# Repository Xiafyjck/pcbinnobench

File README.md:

# PCBInnoBench

PCBInnoBench is an executable PCB design benchmark for LLM agents. This release contains a curated 35-task subset packaged for Forge runs. Each task asks an agent to modify a KiCad project in place and is evaluated against hidden task validators.

## Repository Layout

- `tasks/`: 35 agent-visible task packages. Each task contains `workspace/`, `prompt.md`, `prompt_with_guidance.md`, and `task.json`; original component PDFs remain under each task workspace when available.
- `evaluation/ground_truths/`: hidden golden KiCad projects used only by validators. Do not copy this directory into an agent sandbox.
- `validators/common/`: shared validator implementation.
- `validators/tasks/`: thin per-task validators that call the shared validator with task-specific file expectations.
- `scripts/create_sandboxes.py`: creates isolated Forge sandboxes.
- `scripts/run_forge.py`: runs Forge on prepared sandboxes.
- `scripts/validate.py`: scores completed sandboxes.

## Run With Forge

Create base-prompt sandboxes:

```bash
uv run python scripts/create_sandboxes.py --variant base --tasks all --out runs/forge_base_35
```

Create guided-prompt sandboxes:

```bash
uv run python scripts/create_sandboxes.py --variant guidance --tasks all --out runs/forge_guidance_35
```

Run Forge:

```bash
uv run python scripts/run_forge.py --root runs/forge_guidance_35 --workers 8 --timeout 5400
```

Score the run:

```bash
uv run python scripts/validate.py --run runs/forge_guidance_35 --write
```

Forge model/provider selection is intentionally left to your Forge configuration. The runner records the selected model label if you pass `--model`, but it does not call Codex CLI or Claude Code.

## Task Format

A task directory has this shape:

```text
tasks/<task_id>/
├── workspace/
├── prompt.md
├── prompt_with_guidance.md
└── task.json
```

`workspace/` is the only directory the evaluated agent should edit. The `prompt_with_guidance.md` file is the guided condition described in the benchmark paper.

## Validator Boundary

The public validator code is split into a maintained common layer and small task-specific wrappers. The hidden golden projects live under `evaluation/ground_truths/` and are intentionally excluded from sandboxes produced by `create_sandboxes.py`.

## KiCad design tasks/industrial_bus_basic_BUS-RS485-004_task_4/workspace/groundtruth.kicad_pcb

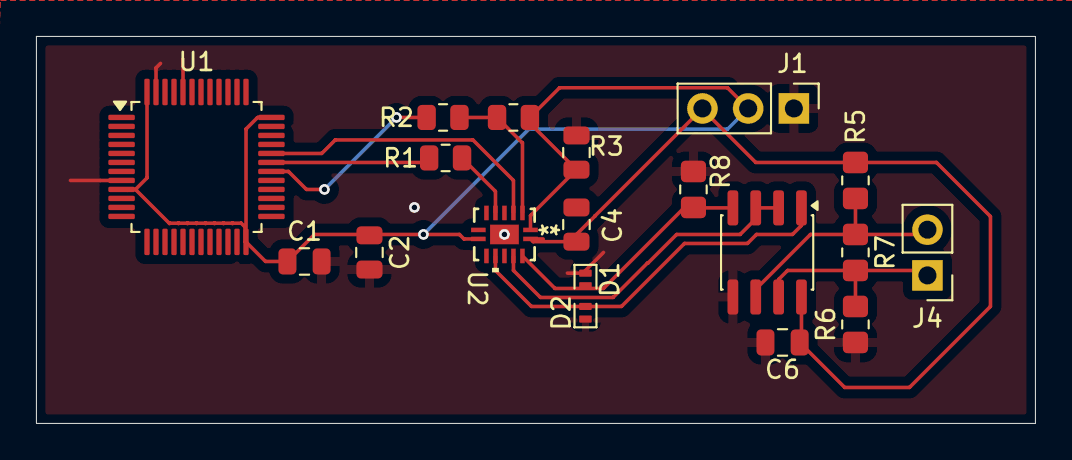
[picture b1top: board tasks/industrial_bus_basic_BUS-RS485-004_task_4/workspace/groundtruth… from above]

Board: 2 copper layers, 55.5 x 21.5 mm, 19 parts (0 on the bottom side), 13 nets.

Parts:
C1, C4, C5: 0.1uf; C_0805_2012Metric
C2: 1uf; C_0805_2012Metric
C6: 2.2uf; C_0805_2012Metric
D1, D2: PESD5V0L1UL; D_SOD-882
J1: Conn_01x03_Pin; PinHeader_1x03_P2.54mm_Vertical
J4: Conn_01x02_Pin; PinHeader_1x02_P2.54mm_Vertical
R1, R2: 50; R_0805_2012Metric
R3: 10k; R_0805_2012Metric
R5, R6: 7.4K; R_0805_2012Metric_Pad1.20x1.40mm_HandSolder
R7: 120; R_0805_2012Metric_Pad1.20x1.40mm_HandSolder
R8: 4.7K; R_0805_2012Metric_Pad1.20x1.40mm_HandSolder
U1: STM32F103C8Tx; LQFP-48_7x7mm_P0.5mm
U2: TXU0304BQAR; QFN_04BQAR_TEX
U3: MAX485E; SOIC-8_3.9x4.9mm_P1.27mm

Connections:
+3V3: C1.1, C2.1, C5.1, J1.2, R3.2, U1.9 (VDDA), U1.24 (VDD), U1.36 (VDD), U1.48 (VDD), U2.1 (VCCA), U2.8 (OE)
+5V: C4.1, C6.2, J1.3, R5.2, U2.14 (VCCB), U3.8 (VCC)
/RS485_5V/RS485_2A: J4.2, R5.1, R7.1, U3.6 (A)
/RS485_5V/RS485_2B: J4.1, R6.2, R7.2, U3.7 (B)
/RS485_5V/RS485_2_DE: U2.12 (B2Y), U3.2 (~RE), U3.3 (DE)
/RS485_5V/RS485_2_RX: D2.2 (A), U2.10 (B4), U3.1 (RO)
/RS485_5V/RS485_2_TX: D1.2 (A), R8.2, U2.13 (B1Y), U3.4 (DI)
/stm32-uart/DE: U1.32 (PA11), U2.3 (A2)
/stm32-uart/RX: R1.2, U2.5 (A4Y)
/stm32-uart/TX: R2.2, R3.1, U2.2 (A1)
GND: C1.2, C2.2, C4.2, C5.2, C6.1, D1.1 (K), D2.1 (K), J1.1, R6.1, R8.1, U1.8 (VSSA), U1.23 (VSS), U1.35 (VSS), U1.44 (BOOT0), U1.47 (VSS), U2.7 (GND), U2.15 (EPAD), U3.5 (GND)
unnamed: R2.1, U1.30 (PA9)
unnamed: R1.1, U1.31 (PA10)

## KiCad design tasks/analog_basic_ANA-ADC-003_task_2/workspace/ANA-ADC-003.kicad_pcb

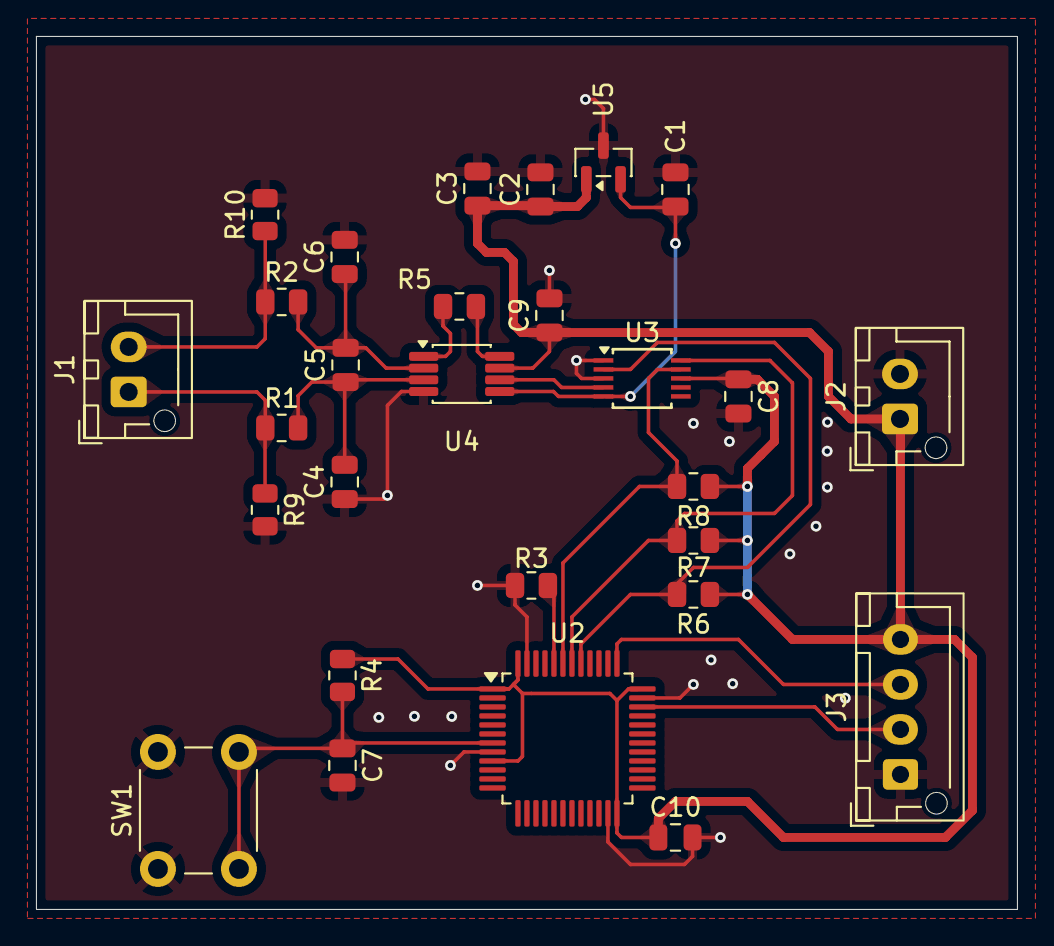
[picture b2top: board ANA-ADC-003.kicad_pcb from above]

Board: 2 copper layers, 54.5 x 48.5 mm, 28 parts (0 on the bottom side), 17 nets.

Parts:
C1: 10uF; C_0805_2012Metric
C2, C8, C9: 0.1uF; C_0805_2012Metric
C3: 1uF; C_0805_2012Metric
C4, C5, C6: 1nF; C_0805_2012Metric
C7, C10: 100nF; C_0805_2012Metric
J1, J2: Conn_01x02_Pin; JST_XH_B2B-XH-AM_1x02_P2.50mm_Vertical
J3: Conn_01x04_Pin; JST_XH_B4B-XH-AM_1x04_P2.50mm_Vertical
R1, R2, R3, R4, R6: 10k; R_0805_2012Metric
R5: 100k; R_0805_2012Metric
R7, R8: 4.7k; R_0805_2012Metric
R9, R10: 10Ω; R_0805_2012Metric
SW1: SW_Push; SW_PUSH_6mm
U2: STM32F103C8Tx; LQFP-48_7x7mm_P0.5mm
U3: ADS1115IDGS; TSSOP-10_3x3mm_P0.5mm
U4: INA333xxDGK; VSSOP-8_3x3mm_P0.65mm
U5: REF3012; SOT-23

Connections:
+3.3V: C2.1, C3.1, C8.1, C9.1, C10.1, J2.1, J3.4, R4.1, R6.1, R7.1, R8.1, U2.1 (VBAT), U2.9 (VDDA), U2.24 (VDD), U2.36 (VDD), U2.48 (VDD), U3.8 (VDD), U4.7 (V+), U5.1 (IN)
/ADC_HIN: J1.1, R1.1, R9.1
/ADC_LIN: J1.2, R2.1, R10.1
/stm32/ADS_ALERT: R6.2, U2.41 (PB5), U3.2 (ALERT/RDY)
/stm32/BOOT0: R3.1, U2.44 (BOOT0)
/stm32/I2C1_SCL: R7.2, U2.42 (PB6), U3.10 (SCL)
/stm32/I2C1_SDA: R8.2, U2.43 (PB7), U3.9 (SDA)
/stm32/NRST: C7.1, R4.2, SW1.2, U2.7 (NRST)
/stm32/swclk: J3.3, U2.37 (PA14)
/stm32/swdio: J3.2, U2.34 (PA13)
/vref: C1.1, U3.5 (AIN1), U4.5 (Ref), U5.2 (OUT)
GND: C1.2, C2.2, C3.2, C4.1, C6.2, C7.2, C8.2, C9.2, C10.2, J2.2, J3.1, R3.2, R9.2, R10.2, SW1.1, U2.8 (VSSA), U2.23 (VSS), U2.35 (VSS), U2.47 (VSS), U3.1 (ADDR), U3.3 (GND), U4.4 (V-), U5.3 (GND)
unnamed: R5.1, U4.8 (Rg)
unnamed: R5.2, U4.1 (Rg)
unnamed: U3.4 (AIN0), U4.6
unnamed: C4.2, C5.1, R1.2, U4.3 (+)
unnamed: C5.2, C6.1, R2.2, U4.2 (-)

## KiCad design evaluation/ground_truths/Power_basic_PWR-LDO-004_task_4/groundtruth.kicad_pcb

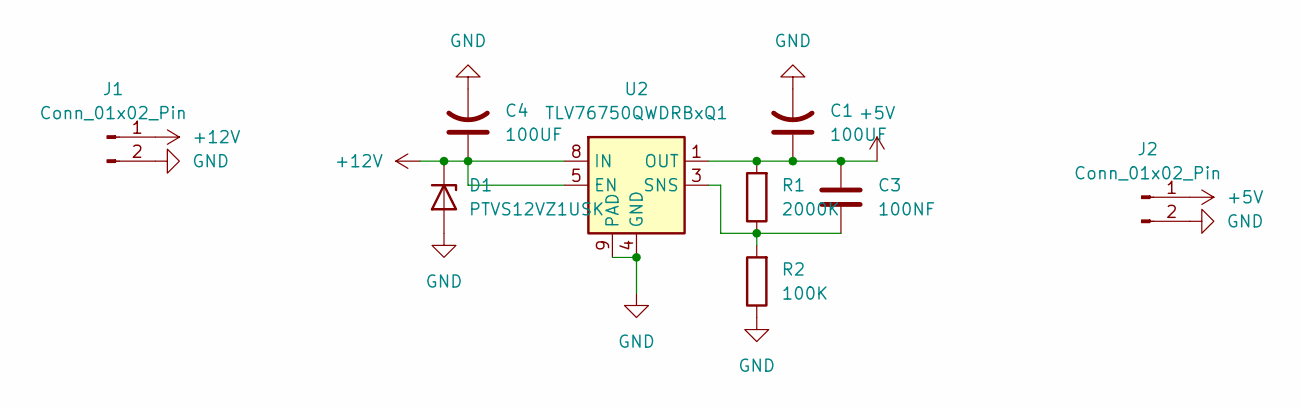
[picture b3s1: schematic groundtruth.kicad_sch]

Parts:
C1, C4: 100UF; C_Elec_3x5.4
C3: 100NF; C_0603_1608Metric
D1: PTVS12VZ1USK; Nexperia_DSN1608-2_1.6x0.8mm
J1, J2: Conn_01x02_Pin; PinHeader_1x02_P2.54mm_Vertical
R1: 2000K; R_0805_2012Metric_Pad1.20x1.40mm_HandSolder
R2: 100K; R_0805_2012Metric_Pad1.20x1.40mm_HandSolder
U2: TLV76750QWDRBxQ1; WSON-8-1EP_2x2mm_P0.5mm_EP0.9x1.6mm

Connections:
+5V: C1.1, C3.1, J2.1, R1.2, U2.1 (OUT)
+12V: C4.1, D1.1 (K), J1.1, U2.5 (EN), U2.8 (IN)
GND: C1.2, C4.2, D1.2 (A), J1.2, J2.2, R2.1, U2.4 (GND), U2.6 (GND), U2.9 (PAD)
unnamed: C3.2, R1.1, R2.2, U2.3 (SNS)

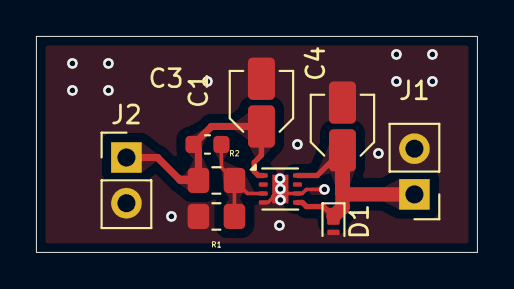
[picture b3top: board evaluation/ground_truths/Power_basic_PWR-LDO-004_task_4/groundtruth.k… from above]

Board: 2 copper layers, 24.5 x 12.0 mm, 9 parts (0 on the bottom side), 4 nets.

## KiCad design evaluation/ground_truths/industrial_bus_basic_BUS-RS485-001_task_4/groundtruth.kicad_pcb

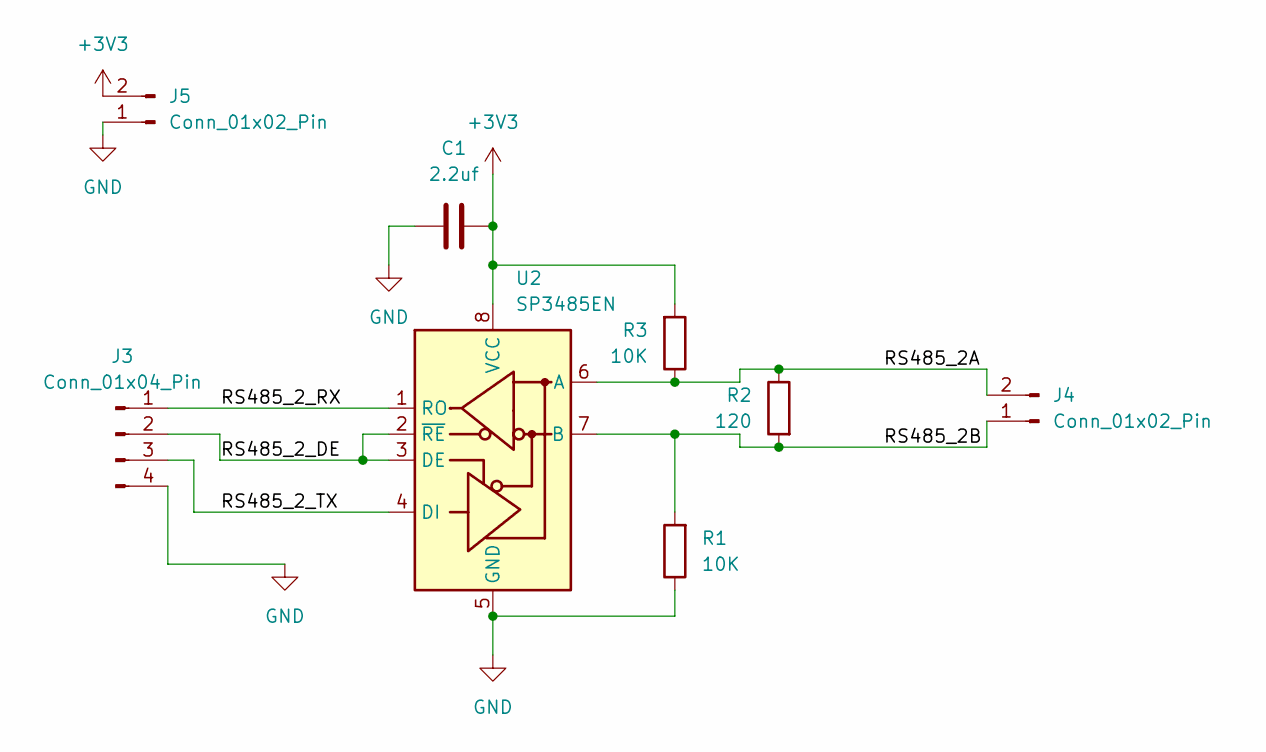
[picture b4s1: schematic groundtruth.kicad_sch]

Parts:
C1: 2.2uf; C_0805_2012Metric
J3: Conn_01x04_Pin; PinHeader_1x04_P2.54mm_Vertical
J4, J5: Conn_01x02_Pin; PinHeader_1x02_P2.54mm_Vertical
R1, R3: 10K; R_0805_2012Metric_Pad1.20x1.40mm_HandSolder
R2: 120; R_0805_2012Metric_Pad1.20x1.40mm_HandSolder
U2: SP3485EN; SOIC-8_3.9x4.9mm_P1.27mm

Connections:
+3V3: C1.2, J5.2, R3.2, U2.8 (VCC)
/RS485_2A: J4.2, R2.1, R3.1, U2.6 (A)
/RS485_2B: J4.1, R1.2, R2.2, U2.7 (B)
/RS485_2_DE: J3.2, U2.2 (~RE), U2.3 (DE)
/RS485_2_RX: J3.1, U2.1 (RO)
/RS485_2_TX: J3.3, U2.4 (DI)
GND: C1.1, J3.4, J5.1, R1.1, U2.5 (GND)

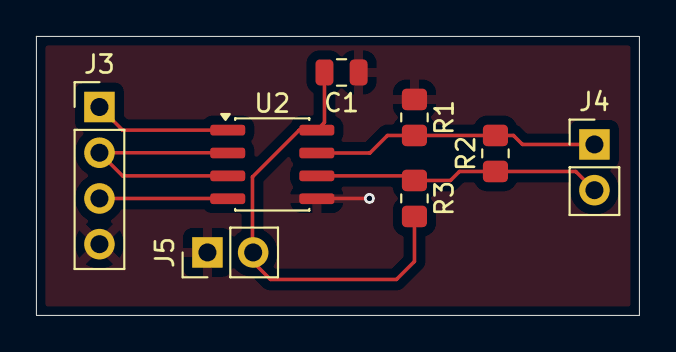
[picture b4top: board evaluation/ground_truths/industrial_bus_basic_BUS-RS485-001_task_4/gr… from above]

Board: 2 copper layers, 33.5 x 15.5 mm, 8 parts (0 on the bottom side), 7 nets.

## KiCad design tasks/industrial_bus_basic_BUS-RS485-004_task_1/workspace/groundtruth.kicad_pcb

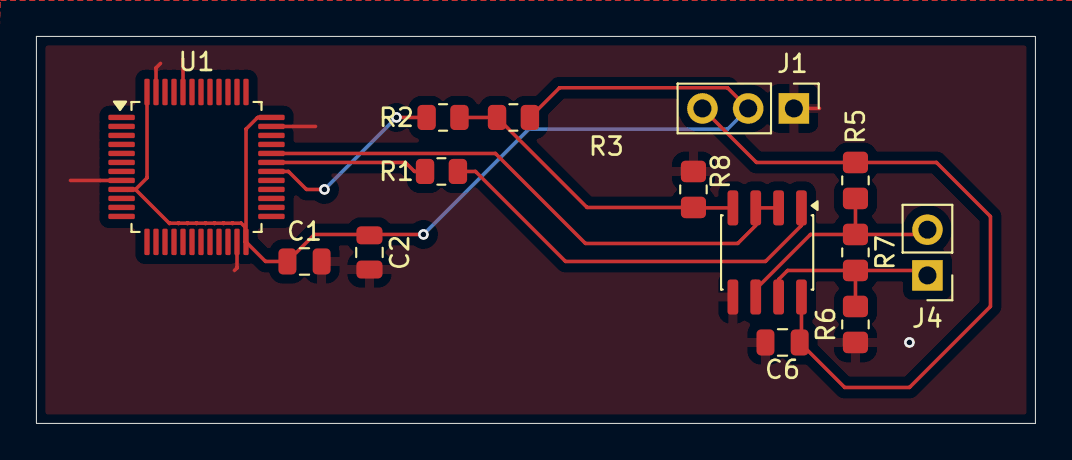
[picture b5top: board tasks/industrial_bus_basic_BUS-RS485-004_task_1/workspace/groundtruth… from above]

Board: 2 copper layers, 55.5 x 21.5 mm, 14 parts (0 on the bottom side), 10 nets.

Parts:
C1: 0.1uf; C_0805_2012Metric
C2: 1uf; C_0805_2012Metric
C6: 2.2uf; C_0805_2012Metric
J1: Conn_01x03_Pin; PinHeader_1x03_P2.54mm_Vertical
J4: Conn_01x02_Pin; PinHeader_1x02_P2.54mm_Vertical
R1, R2: 50; R_0805_2012Metric
R3: 10k; R_0805_2012Metric
R5, R6: 7.4K; R_0805_2012Metric_Pad1.20x1.40mm_HandSolder
R7: 120; R_0805_2012Metric_Pad1.20x1.40mm_HandSolder
R8: 4.7K; R_0805_2012Metric_Pad1.20x1.40mm_HandSolder
U1: STM32F103C8Tx; LQFP-48_7x7mm_P0.5mm
U3: MAX485E; SOIC-8_3.9x4.9mm_P1.27mm

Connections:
+3V3: C1.1, C2.1, J1.2, R3.2, U1.9 (VDDA), U1.24 (VDD), U1.36 (VDD), U1.48 (VDD)
+5V: C6.2, J1.3, R5.2, U3.8 (VCC)
/RS485_5V/RS485_2A: J4.2, R5.1, R7.1, U3.6 (A)
/RS485_5V/RS485_2B: J4.1, R6.2, R7.2, U3.7 (B)
/RS485_5V/RS485_2_DE: U1.32 (PA11), U3.2 (~RE), U3.3 (DE)
/RS485_5V/RS485_2_RX: R1.2, U3.1 (RO)
/RS485_5V/RS485_2_TX: R2.2, R3.1, R8.2, U3.4 (DI)
GND: C1.2, C2.2, C6.1, J1.1, R6.1, R8.1, U1.8 (VSSA), U1.23 (VSS), U1.35 (VSS), U1.44 (BOOT0), U1.47 (VSS), U3.5 (GND)
unnamed: R2.1, U1.30 (PA9)
unnamed: R1.1, U1.31 (PA10)

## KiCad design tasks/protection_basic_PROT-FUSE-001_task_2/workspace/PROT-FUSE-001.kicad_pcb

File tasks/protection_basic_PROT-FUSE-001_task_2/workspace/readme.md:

# PROT-FUSE-001

Use unidirectional TVS to protect input 5V.

Includes fuse design.

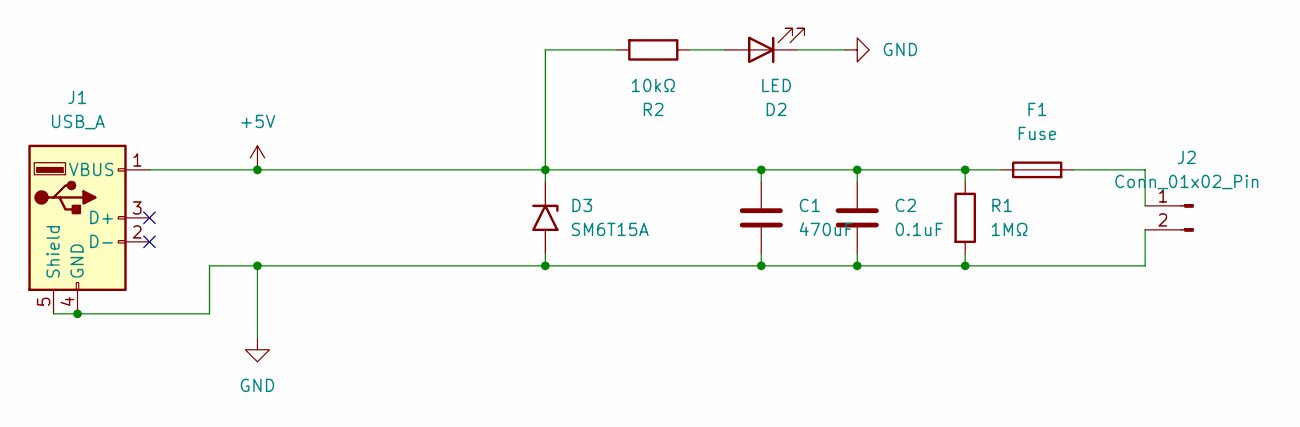
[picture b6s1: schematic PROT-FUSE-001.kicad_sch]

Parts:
C1: 470uF; C_Disc_D9.0mm_W5.0mm_P10.00mm
C2: 0.1uF; C_0805_2012Metric
D2: LED; LED_0805_2012Metric
D3: SM6T15A; D_SMB
F1: Fuse; Fuse_1210_3225Metric
J1: USB_A; USB_A_TE_292303-7_Horizontal
J2: Conn_01x02_Pin; JST_EH_B2B-EH-A_1x02_P2.50mm_Vertical
R1: 1MΩ; R_0805_2012Metric
R2: 10kΩ; R_0805_2012Metric

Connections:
+5V: C1.1, C2.1, D3.1 (A1), F1.1, J1.1 (VBUS), R1.1, R2.2
GND: C1.2, C2.2, D2.1 (K), D3.2 (A2), J1.4 (GND), J1.5 (Shield), J2.2, R1.2
unnamed: D2.2 (A), R2.1
unnamed: F1.2, J2.1

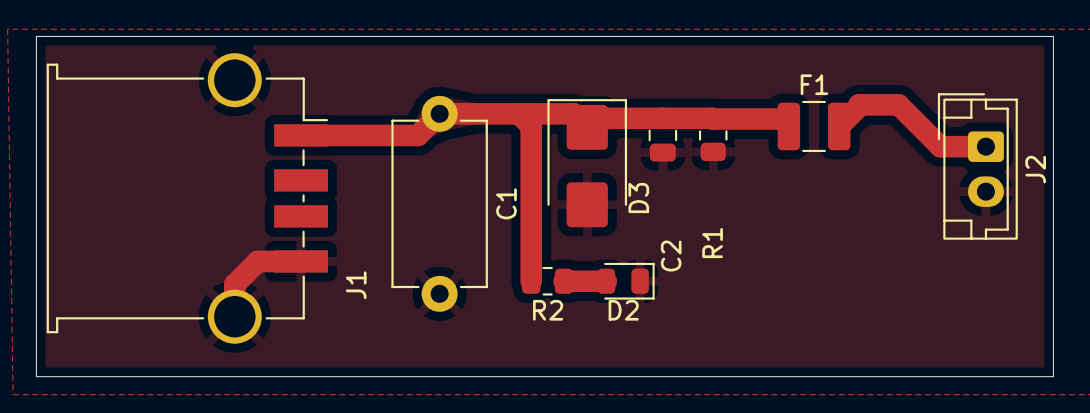
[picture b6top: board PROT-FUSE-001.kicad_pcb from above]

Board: 2 copper layers, 56.5 x 18.9 mm, 9 parts (0 on the bottom side), 4 nets.

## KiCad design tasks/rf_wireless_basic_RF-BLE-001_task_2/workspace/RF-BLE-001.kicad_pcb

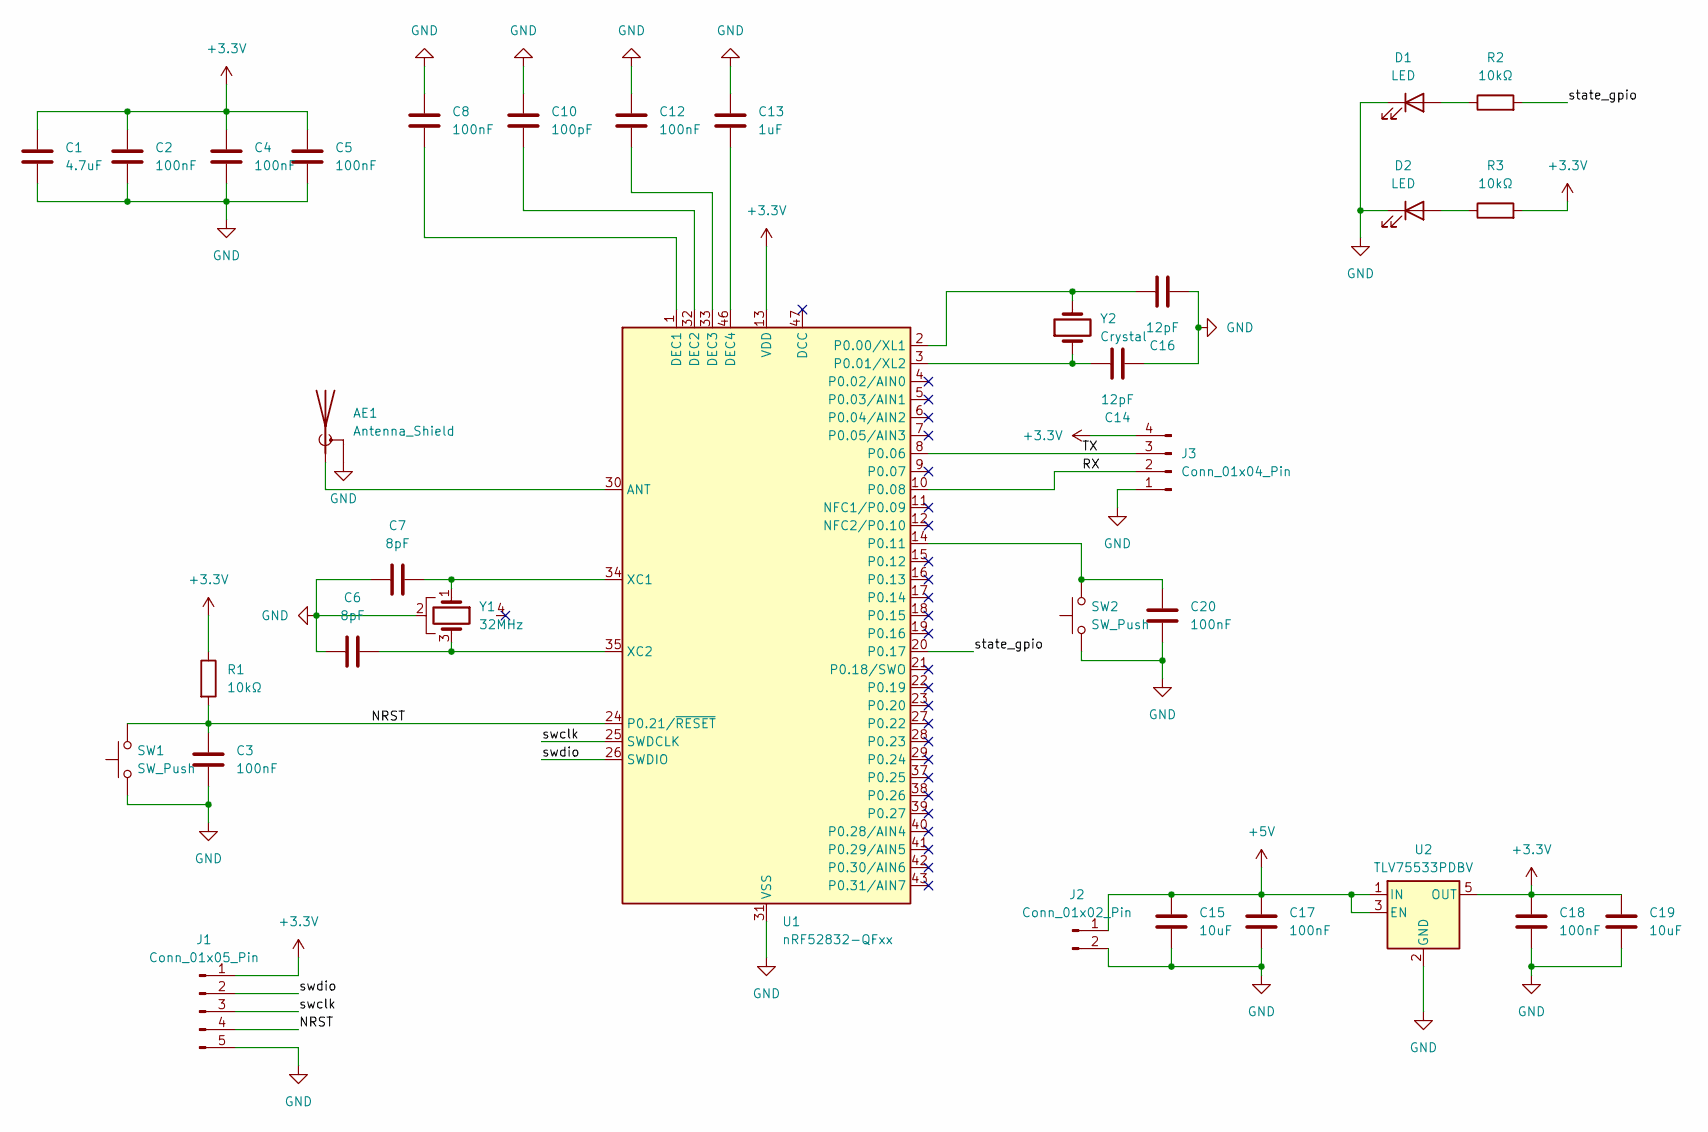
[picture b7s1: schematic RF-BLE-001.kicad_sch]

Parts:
AE1: Antenna_Shield; Texas_SWRA117D_2.4GHz_Right
C1: 4.7uF; C_0805_2012Metric
C2, C3, C4, C5, C8, C12, C17, C18, C20: 100nF; C_0805_2012Metric
C6, C7: 8pF; C_0805_2012Metric
C10: 100pF; C_0805_2012Metric
C13: 1uF; C_0805_2012Metric
C14, C16: 12pF; C_0805_2012Metric
C15, C19: 10uF; C_0805_2012Metric
D1, D2: LED; LED_0805_2012Metric
J1: Conn_01x05_Pin; JST_XH_B5B-XH-A_1x05_P2.50mm_Vertical
J2: Conn_01x02_Pin; JST_EH_B2B-EH-A_1x02_P2.50mm_Vertical
J3: Conn_01x04_Pin; JST_XH_B4B-XH-A_1x04_P2.50mm_Vertical
R1, R2, R3: 10kΩ; R_0805_2012Metric
SW1, SW2: SW_Push; SW_PUSH_6mm
U1: nRF52832-QFxx; QFN-48-1EP_6x6mm_P0.4mm_EP4.6x4.6mm
U2: TLV75533PDBV; SOT-23-5
Y1: 32MHz; Crystal_SMD_Abracon_ABM8AIG-4Pin_3.2x2.5mm
Y2: Crystal; Crystal_HC49-4H_Vertical

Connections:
+3.3V: C1.1, C2.1, C4.1, C5.1, C18.1, C19.1, J1.1, J3.4, R1.1, R3.2, U1.13 (VDD), U1.36 (VDD), U1.48 (VDD), U2.5 (OUT)
+5V: C15.1, C17.1, J2.1, U2.1 (IN), U2.3 (EN)
/NRST: C3.1, J1.4, R1.2, SW1.2, U1.24 (P0.21/~RESET)
/RX: J3.2, U1.10 (P0.08)
/TX: J3.3, U1.8 (P0.06)
/state_gpio: R2.2, U1.20 (P0.17)
/swclk: J1.3, U1.25 (SWDCLK)
/swdio: J1.2, U1.26 (SWDIO)
GND: AE1.2 (Shield), C1.2, C2.2, C3.2, C4.2, C5.2, C6.1, C7.1, C8.1, C10.1, C12.1, C13.1, C14.1, C15.2, C16.1, C17.2, C18.2, C19.2, C20.2, D1.1 (K), D2.1 (K), J1.5, J2.2, J3.1, SW1.1, SW2.1, U1.31 (VSS), U1.45 (VSS), U1.49 (VSS), U2.2 (GND), Y1.2
unnamed: AE1.1 (A), U1.30 (ANT)
unnamed: D1.2 (A), R2.1
unnamed: D2.2 (A), R3.1
unnamed: C8.2, U1.1 (DEC1)
unnamed: C10.2, U1.32 (DEC2)
unnamed: C12.2, U1.33 (DEC3)
unnamed: C13.2, U1.46 (DEC4)
unnamed: C16.2, U1.2 (P0.00/XL1), Y2.2
unnamed: C14.2, U1.3 (P0.01/XL2), Y2.1
unnamed: C20.1, SW2.2, U1.14 (P0.11)
unnamed: C7.2, U1.34 (XC1), Y1.1
unnamed: C6.2, U1.35 (XC2), Y1.3

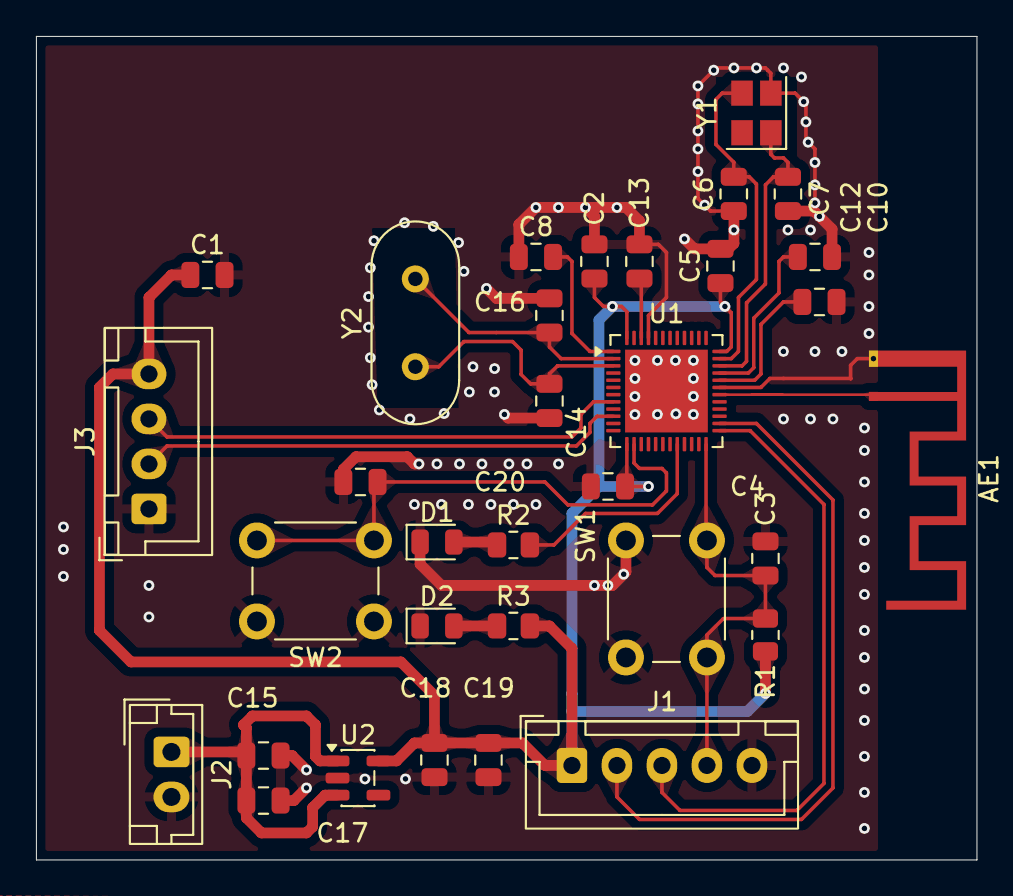
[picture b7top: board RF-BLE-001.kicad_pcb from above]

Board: 4 copper layers, 52.2 x 45.8 mm, 33 parts (0 on the bottom side), 21 nets.

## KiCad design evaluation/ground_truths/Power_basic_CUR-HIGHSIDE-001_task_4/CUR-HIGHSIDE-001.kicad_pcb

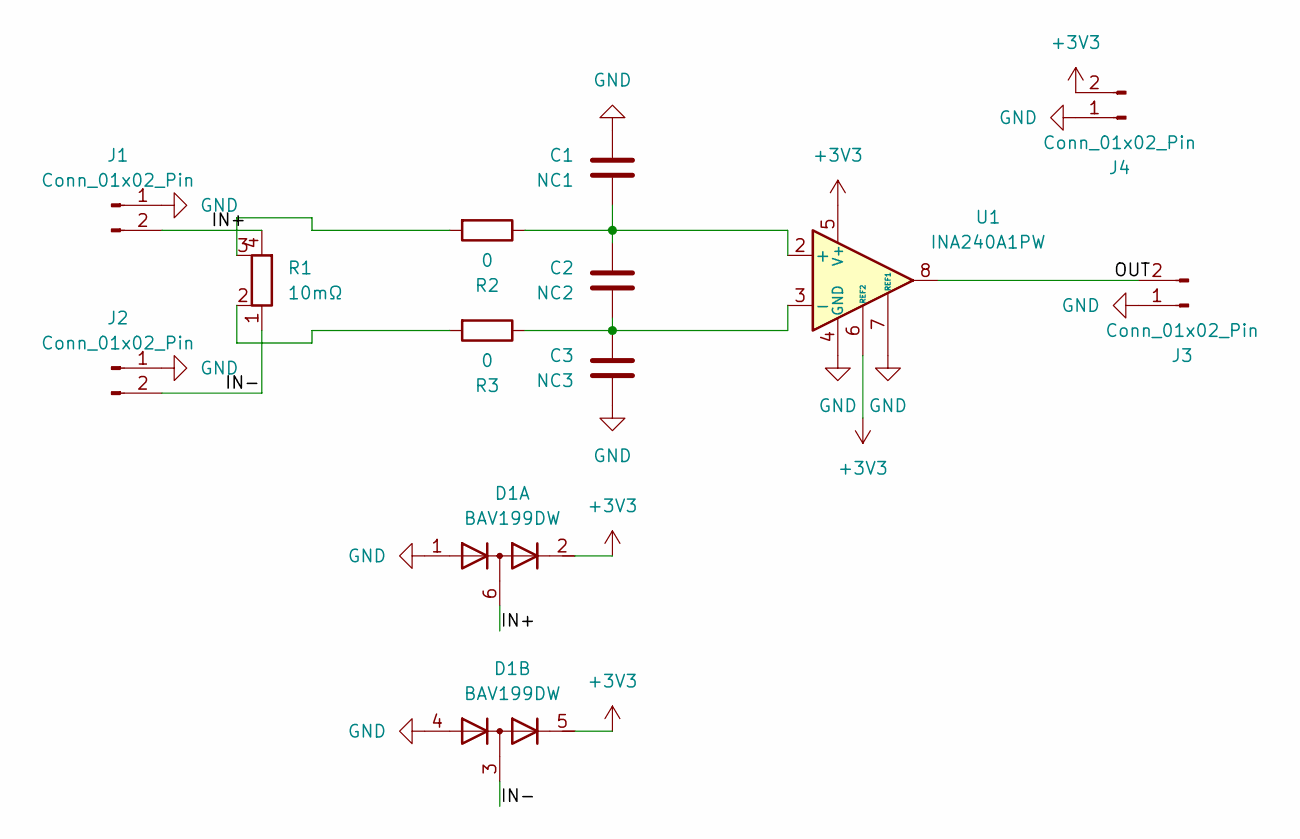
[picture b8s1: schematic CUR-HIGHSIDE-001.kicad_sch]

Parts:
D1: BAV199DW; SOT-363_SC-70-6
J1, J2, J3, J4: Conn_01x02_Pin; JST_EH_B2B-EH-A_1x02_P2.50mm_Vertical
NC1: C1; C_0805_2012Metric
NC2: C2; C_0805_2012Metric
NC3: C3; C_0805_2012Metric
R1: 10mΩ; R_Shunt_Isabellenhuette_BVR4026
R2, R3: 0; R_0805_2012Metric
U1: INA240A1PW; TSSOP-8_4.4x3mm_P0.65mm

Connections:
+3V3: D1.2 (K2), D1.5 (K4), J4.2, U1.5 (V+), U1.6 (REF2)
/IN+: D1.6 (K3A4), J1.2, R1.4
/IN-: D1.3 (K1A2), J2.2, R1.1
/OUT: J3.2, U1.8
GND: D1.1 (A1), D1.4 (A3), J1.1, J2.1, J3.1, J4.1, NC1.2, NC3.1, U1.1 (GND), U1.4 (GND), U1.7 (REF1)
unnamed: R1.2, R3.2
unnamed: R1.3, R2.2
unnamed: NC1.1, NC2.2, R2.1, U1.2 (+)
unnamed: NC2.1, NC3.2, R3.1, U1.3 (-)

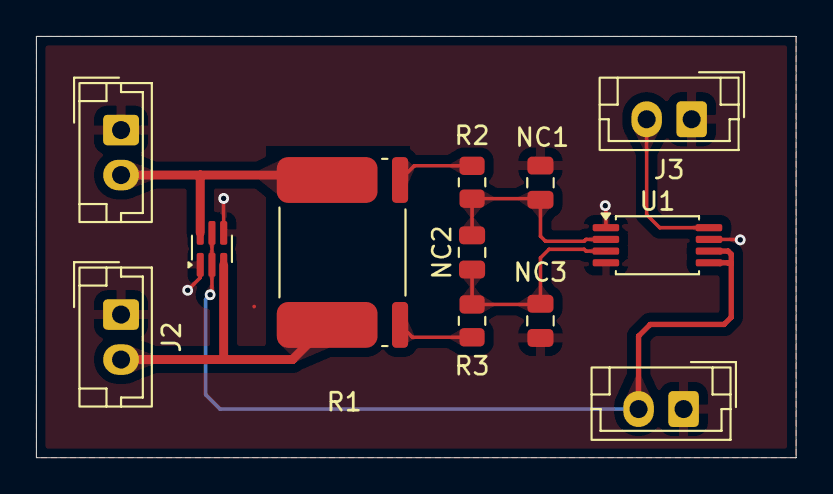
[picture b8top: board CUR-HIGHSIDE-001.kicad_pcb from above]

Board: 2 copper layers, 42.2 x 23.4 mm, 12 parts (0 on the bottom side), 9 nets.

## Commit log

2026-05-07 init
